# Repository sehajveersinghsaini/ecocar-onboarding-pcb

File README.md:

# EcoCar Onboarding PCB (STM32F103)

My onboarding board for the EcoCar team (Electrical), 2026–27 season. It's an STM32F103C8T6 development board powered and programmed over USB-C/SWD, with 10 LEDs, buttons, a potentiometer and headers for I2C, SPI and UART.

**Status:** design finished and checked (ERC 0, DRC 0, schematic/PCB parity 0). Waiting for the Electrical Lead's review before ordering. Assembly and firmware come next.

## What's on the board

| Block | Parts | Notes |
|---|---|---|
| MCU | U1 STM32F103C8T6 (LQFP-48) | 8 MHz crystal Y1 with 20 pF load caps (C10, C11) |
| Power | J3 USB-C, U2 AMS1117-3.3 | 5 V from USB → 3.3 V. C8 10 µF in, C9 22 µF out |
| Decoupling | C1–C4 100 nF, C5 4.7 µF | One 100 nF right next to each VDD/VBAT pin |
| Analog supply | FB1 ferrite bead, C6 10 nF, C7 1 µF | Filters 3.3 V into VDDA |
| USB | R3, R4 5.1 kΩ on CC1/CC2, R5 1.5 kΩ D+ pull-up | USB full speed on PA11/PA12 |
| Programming | J2 SWD header, SW1 reset, J1 BOOT0 jumper | R1/R2 10 kΩ pull-downs on BOOT0/BOOT1 |
| LEDs | D1–D10 (4 red, 3 yellow, 3 green), 330 Ω each | D6–D10 are on timer channels for PWM |
| Inputs | SW2–SW4 push buttons, RV1 10 kΩ potentiometer | Buttons use internal pull-ups; pot goes to ADC PA0 |
| Headers | J4 OLED (I2C1), J5 SPI2, J6 UART1, J7 I2C2, J8 power | 4.7 kΩ pull-ups on both I2C buses (R16–R19) |

## Pin map

| MCU pin | Function | Connected to |
|---|---|---|
| PA0 | ADC1_IN0 | RV1 wiper |
| PA1–PA5 | GPIO out | LED1–LED5 (D1–D5) |
| PA6, PA7, PB0, PB1, PA8 | TIM PWM | LED_PWM1–5 (D6–D10) |
| PA9 / PA10 | USART1 TX / RX | J6 |
| PA11 / PA12 | USB D− / D+ | J3 |
| PA13 / PA14 | SWDIO / SWCLK | J2 |
| PB5, PB8, PB9 | GPIO in | BTN1–BTN3 (SW2–SW4) |
| PB6 / PB7 | I2C1 SCL / SDA | J4 (OLED) |
| PB10 / PB11 | I2C2 SCL / SDA | J7 |
| PB12–PB15 | SPI2 CS / SCK / MISO / MOSI | J5 |
| PD0 / PD1 | HSE in / out | Y1 8 MHz |

## Header pinouts (pin 1 first)

- **J2 SWD:** 3V3, SWCLK, SWDIO, NRST, GND
- **J4 OLED:** GND, 3V3, SCL, SDA
- **J5 SPI2:** GND, 3V3, SCK, MISO, MOSI, CS
- **J6 UART1:** GND, TX, RX
- **J7 I2C2:** GND, 3V3, SCL, SDA
- **J8 Power:** 5V, 5V, 3V3, 3V3, GND, GND
- **J1 BOOT0:** BOOT0, 3V3 (jumper on = boot from system memory)

## Layout

- 80 × 60 mm, 2 layers, 1.6 mm FR4
- Ground pour on both layers, stitched with vias across the board
- Top layer routes horizontally, bottom layer vertically, with vias to change direction (short fan-outs at the pins)
- Signal traces 0.25 mm, 3.3 V 0.4 mm, 5 V 0.5 mm, 0.2 mm clearance
- 0603 or larger passives, no BGA
- The USB-C connector's mouth sits flush with the right edge. Its silkscreen line was trimmed so it doesn't hang off the board, which is why there's one DRC exclusion (library mismatch on J3).

## Files

- `hardware/ecocar_onboarding/` — KiCad 10 project (schematic, PCB, schematic PDF)
- `firmware/ecocar_onboarding.ioc` — STM32CubeMX pin configuration
- `docs/board_3d.png` — 3D render

## How it was made

Following the Phil's Lab KiCad STM32 tutorial and the EcoCar onboarding requirements.

## Next steps

1. Design review with the Electrical Lead
2. Order the board and solder it by hand
3. Firmware in STM32CubeIDE: LED patterns, potentiometer → PWM brightness, buttons, USB serial messages, OLED

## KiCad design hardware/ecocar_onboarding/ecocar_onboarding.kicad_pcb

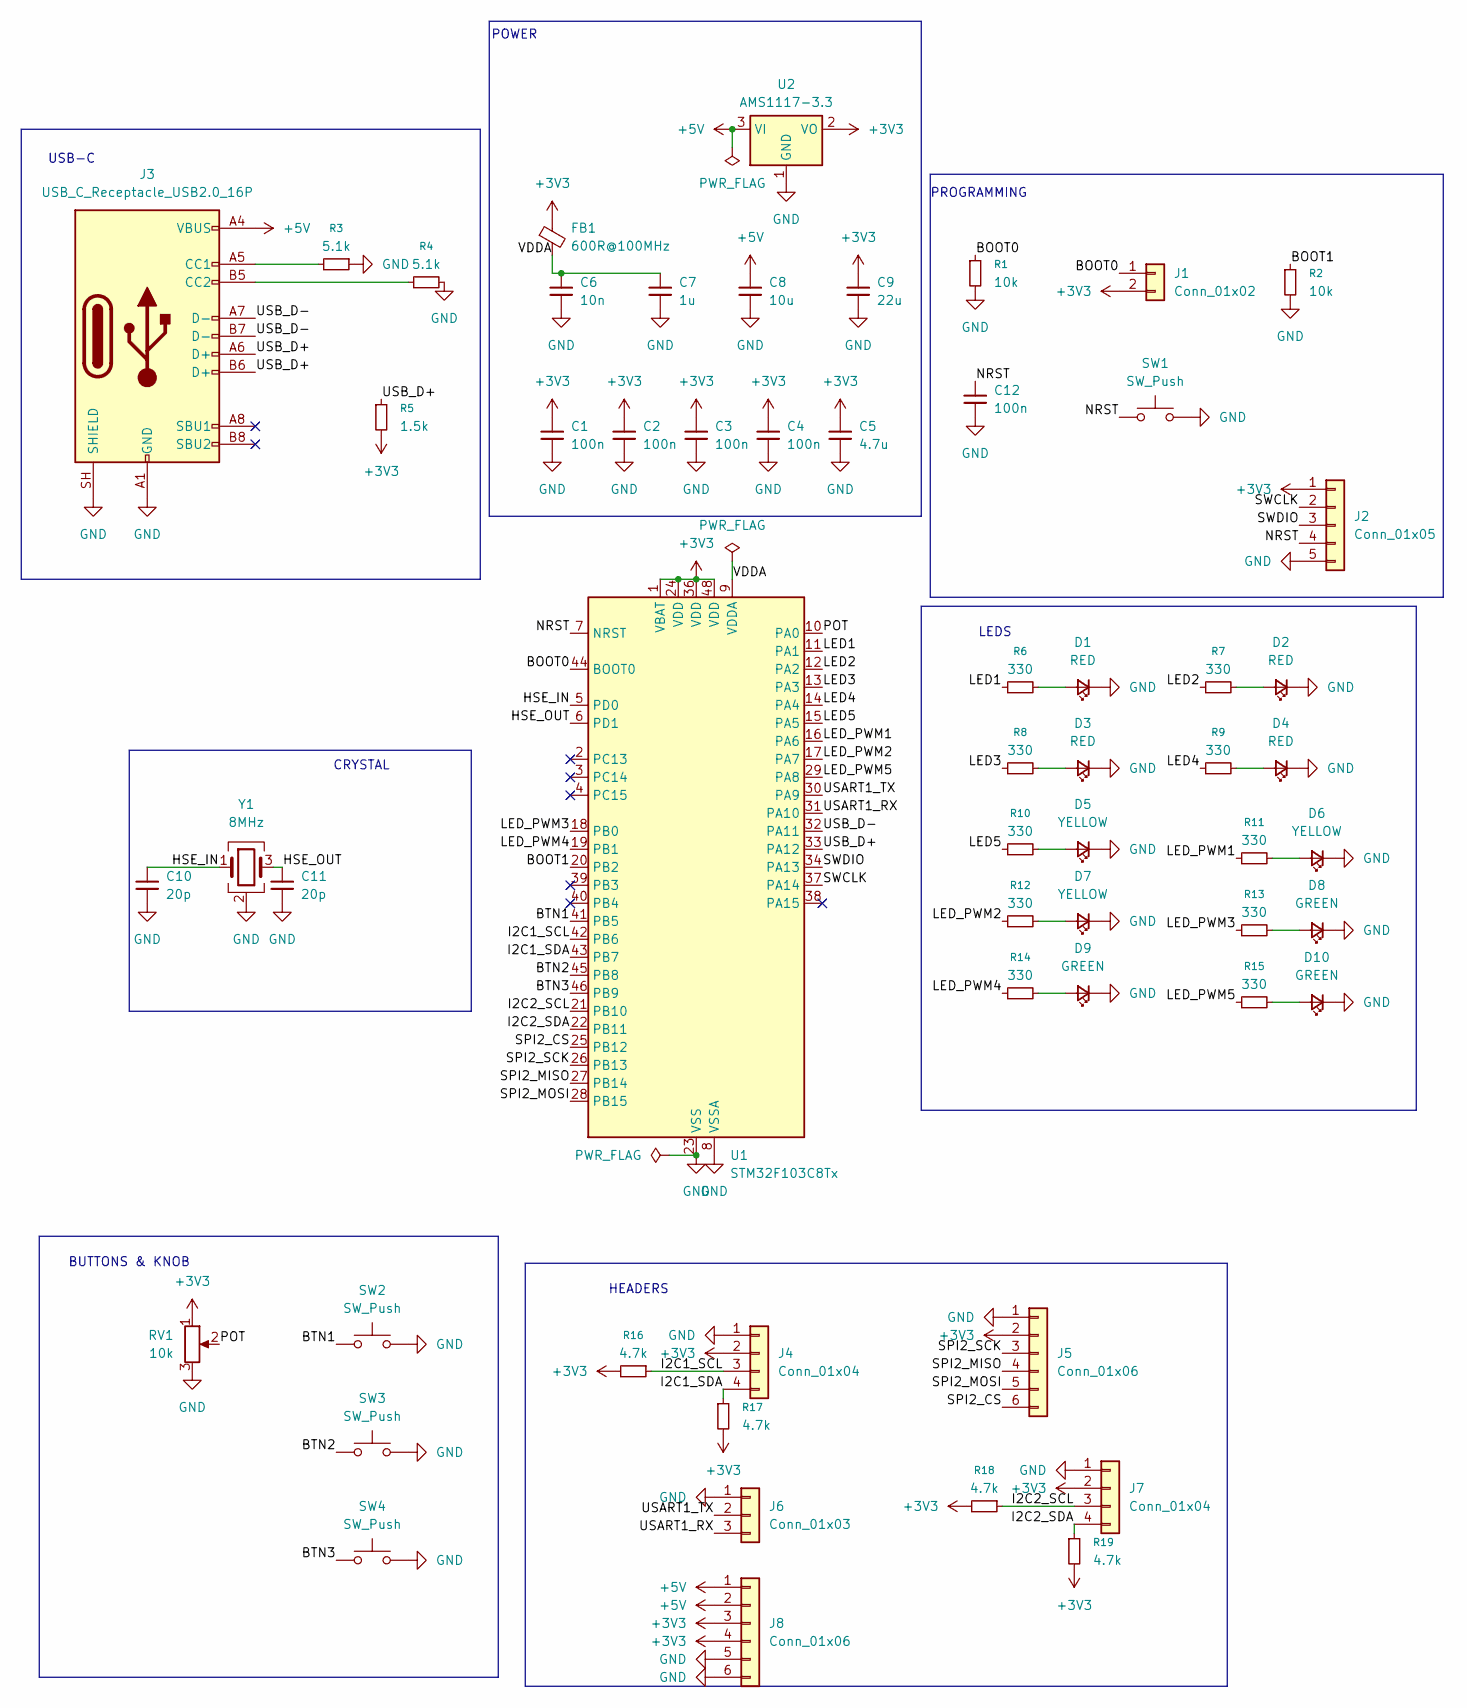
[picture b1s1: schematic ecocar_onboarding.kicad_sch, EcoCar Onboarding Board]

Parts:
C1, C2, C3, C4, C12: 100n; C_0603_1608Metric
C5: 4.7u; C_0805_2012Metric
C6: 10n; C_0603_1608Metric
C7: 1u; C_0603_1608Metric
C8: 10u; C_0805_2012Metric
C9: 22u; C_0805_2012Metric
C10, C11: 20p; C_0603_1608Metric
D1, D2, D3, D4: RED; LED_0603_1608Metric
D5, D6, D7: YELLOW; LED_0603_1608Metric
D8, D9, D10: GREEN; LED_0603_1608Metric
FB1: 600R@100MHz; L_0603_1608Metric
J1: Conn_01x02; PinHeader_1x02_P2.54mm_Vertical
J2: Conn_01x05; PinHeader_1x05_P2.54mm_Vertical
J3: USB_C_Receptacle_USB2.0_16P; USB_C_Receptacle_HRO_TYPE-C-31-M-12
J4, J7: Conn_01x04; PinHeader_1x04_P2.54mm_Vertical
J5, J8: Conn_01x06; PinHeader_1x06_P2.54mm_Vertical
J6: Conn_01x03; PinHeader_1x03_P2.54mm_Vertical
R1, R2: 10k; R_0603_1608Metric
R3, R4: 5.1k; R_0603_1608Metric
R5: 1.5k; R_0603_1608Metric
R6, R7, R8, R9, R10, R11, R12, R13, R14, R15: 330; R_0603_1608Metric
R16, R17, R18, R19: 4.7k; R_0603_1608Metric
RV1: 10k; Potentiometer_Bourns_3386P_Vertical
SW1, SW2, SW3, SW4: SW_Push; SW_PUSH_6mm
U1: STM32F103C8Tx; LQFP-48_7x7mm_P0.5mm
U2: AMS1117-3.3; SOT-223-3_TabPin2
Y1: 8MHz; Crystal_SMD_3225-4Pin_3.2x2.5mm

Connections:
+3V3: C1.1, C2.1, C3.1, C4.1, C5.1, C9.1, FB1.1, J1.2, J2.1, J4.2, J5.2, J7.2, J8.3, J8.4, R5.2, R16.2, R17.2, R18.2, R19.2, RV1.1, U1.1 (VBAT), U1.24 (VDD), U1.36 (VDD), U1.48 (VDD), U2.2 (VO)
+5V: C8.1, J3.A4 (VBUS), J3.A9 (VBUS), J3.B4 (VBUS), J3.B9 (VBUS), J8.1, J8.2, U2.3 (VI)
/BOOT0: J1.1, R1.1, U1.44 (BOOT0)
/BOOT1: R2.1, U1.20 (PB2)
/BTN1: SW2.1, U1.41 (PB5)
/BTN2: SW3.1, U1.45 (PB8)
/BTN3: SW4.1, U1.46 (PB9)
/HSE_IN: C10.1, U1.5 (PD0), Y1.1
/HSE_OUT: C11.1, U1.6 (PD1), Y1.3
/I2C1_SCL: J4.3, R16.1, U1.42 (PB6)
/I2C1_SDA: J4.4, R17.1, U1.43 (PB7)
/I2C2_SCL: J7.3, R18.1, U1.21 (PB10)
/I2C2_SDA: J7.4, R19.1, U1.22 (PB11)
/LED1: R6.1, U1.11 (PA1)
/LED2: R7.1, U1.12 (PA2)
/LED3: R8.1, U1.13 (PA3)
/LED4: R9.1, U1.14 (PA4)
/LED5: R10.1, U1.15 (PA5)
/LED_PWM1: R11.1, U1.16 (PA6)
/LED_PWM2: R12.1, U1.17 (PA7)
/LED_PWM3: R13.1, U1.18 (PB0)
/LED_PWM4: R14.1, U1.19 (PB1)
/LED_PWM5: R15.1, U1.29 (PA8)
/NRST: C12.1, J2.4, SW1.1, U1.7 (NRST)
/POT: RV1.2, U1.10 (PA0)
/SPI2_CS: J5.6, U1.25 (PB12)
/SPI2_MISO: J5.4, U1.27 (PB14)
/SPI2_MOSI: J5.5, U1.28 (PB15)
/SPI2_SCK: J5.3, U1.26 (PB13)
/SWCLK: J2.2, U1.37 (PA14)
/SWDIO: J2.3, U1.34 (PA13)
/USART1_RX: J6.3, U1.31 (PA10)
/USART1_TX: J6.2, U1.30 (PA9)
/USB_D+: J3.A6 (D+), J3.B6 (D+), R5.1, U1.33 (PA12)
/USB_D-: J3.A7 (D-), J3.B7 (D-), U1.32 (PA11)
/VDDA: C6.1, C7.1, FB1.2, U1.9 (VDDA)
GND: C1.2, C2.2, C3.2, C4.2, C5.2, C6.2, C7.2, C8.2, C9.2, C10.2, C11.2, C12.2, D1.1 (K), D2.1 (K), D3.1 (K), D4.1 (K), D5.1 (K), D6.1 (K), D7.1 (K), D8.1 (K), D9.1 (K), D10.1 (K), J2.5, J3.A1 (GND), J3.A12 (GND), J3.B1 (GND), J3.B12 (GND), J3.SH (SHIELD), J4.1, J5.1, J6.1, J7.1, J8.5, J8.6, R1.2, R2.2, R3.1, R4.2, RV1.3, SW1.2, SW2.2, SW3.2, SW4.2, U1.8 (VSSA), U1.23 (VSS), U1.35 (VSS), U1.47 (VSS), U2.1 (GND), Y1.2 (G), Y1.4 (G)
unnamed: D1.2 (A), R6.2
unnamed: D2.2 (A), R7.2
unnamed: D3.2 (A), R8.2
unnamed: D4.2 (A), R9.2
unnamed: D5.2 (A), R10.2
unnamed: D6.2 (A), R11.2
unnamed: D7.2 (A), R12.2
unnamed: D8.2 (A), R13.2
unnamed: D9.2 (A), R14.2
unnamed: D10.2 (A), R15.2
unnamed: J3.A5 (CC1), R3.2
unnamed: J3.B5 (CC2), R4.1

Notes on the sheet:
PROGRAMMING
POWER
CRYSTAL
USB-C
HEADERS
BUTTONS & KNOB
LEDS

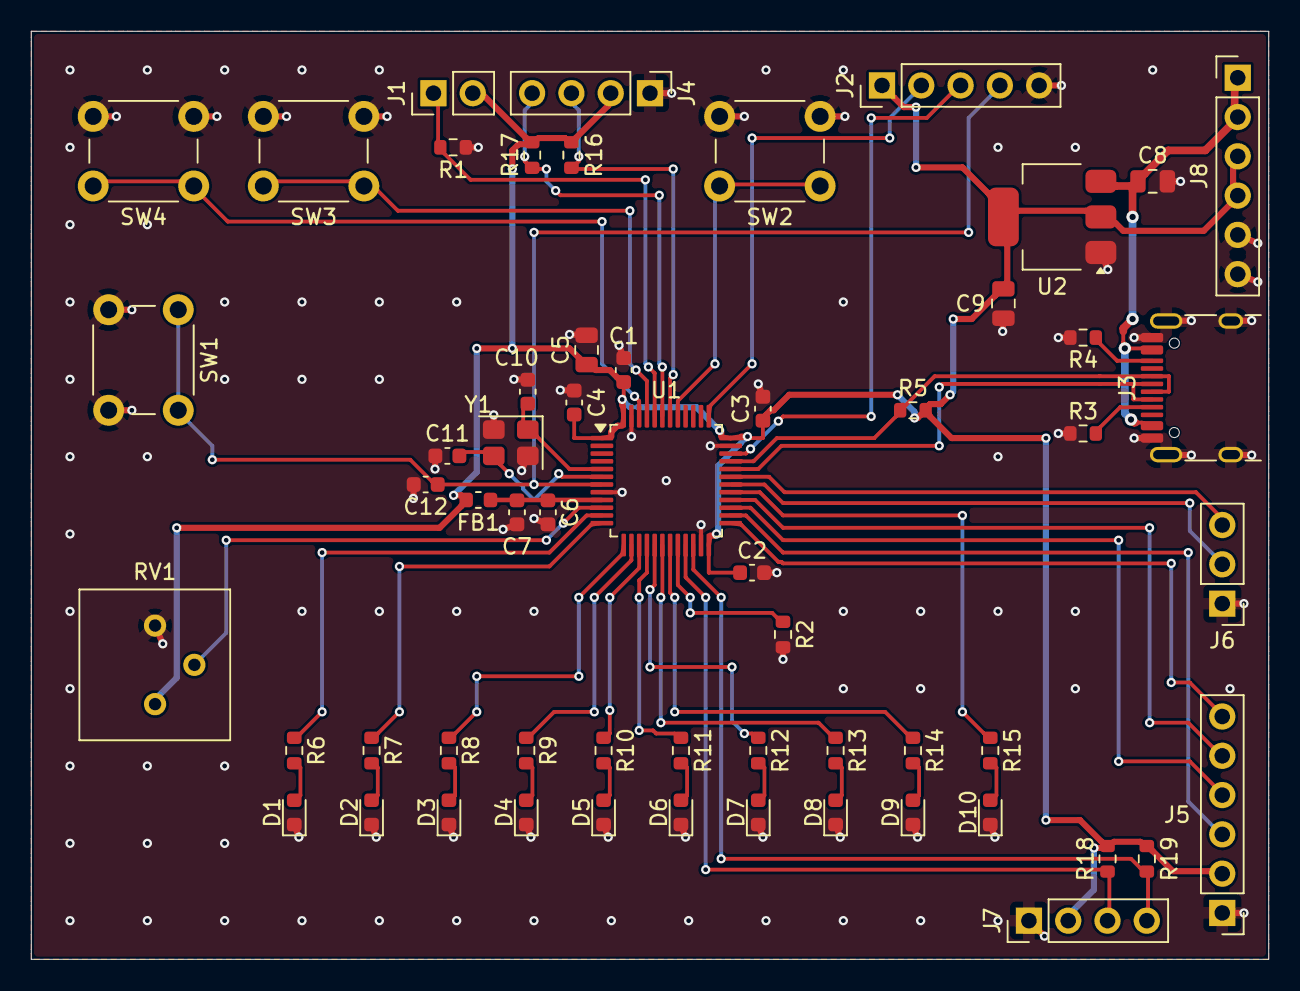
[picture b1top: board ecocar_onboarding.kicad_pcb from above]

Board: 2 copper layers, 80.0 x 60.0 mm, 58 parts (0 on the bottom side), 49 nets.

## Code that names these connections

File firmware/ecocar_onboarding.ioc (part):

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Mcu.Name=STM32F103C(8-B)Tx
Mcu.Package=LQFP48
Mcu.UserName=STM32F103C8Tx
PA0-WKUP.GPIOParameters=GPIO_Label
PA0-WKUP.GPIO_Label=POT
PA0-WKUP.Signal=ADCx_IN0
PA1.GPIOParameters=GPIO_Label
PA1.GPIO_Label=LED1
PA1.Signal=GPIO_Output
PA10.Mode=Asynchronous
PA10.Signal=USART1_RX
PA11.Mode=Device
PA11.Signal=USB_DM
PA12.Mode=Device
PA12.Signal=USB_DP
PA13.Mode=Serial_Wire
PA13.Signal=SYS_JTMS-SWDIO
PA14.Mode=Serial_Wire
PA14.Signal=SYS_JTCK-SWCLK
PA2.GPIOParameters=GPIO_Label
PA2.GPIO_Label=LED2
PA2.Signal=GPIO_Output
PA3.GPIOParameters=GPIO_Label
PA3.GPIO_Label=LED3
PA3.Signal=GPIO_Output
PA4.GPIOParameters=GPIO_Label
PA4.GPIO_Label=LED4
PA4.Signal=GPIO_Output
PA5.GPIOParameters=GPIO_Label
PA5.GPIO_Label=LED5
PA5.Signal=GPIO_Output
PA6.GPIOParameters=GPIO_Label
PA6.GPIO_Label=LED_PWM1
PA6.Signal=S_TIM3_CH1
PA7.GPIOParameters=GPIO_Label
PA7.GPIO_Label=LED_PWM2
PA7.Signal=S_TIM3_CH2
PA8.GPIOParameters=GPIO_Label
PA8.GPIO_Label=LED_PWM5
PA8.Signal=S_TIM1_CH1
PA9.Mode=Asynchronous
PA9.Signal=USART1_TX
PB0.GPIOParameters=GPIO_Label
PB0.GPIO_Label=LED_PWM3
PB0.Signal=S_TIM3_CH3
PB1.GPIOParameters=GPIO_Label
PB1.GPIO_Label=LED_PWM4
PB1.Signal=S_TIM3_CH4
PB10.Mode=I2C
PB10.Signal=I2C2_SCL
PB11.Mode=I2C
PB11.Signal=I2C2_SDA
PB12.GPIOParameters=GPIO_Label
PB12.GPIO_Label=SPI2_CS
PB12.Signal=GPIO_Output
PB13.Mode=Full_Duplex_Master
PB13.Signal=SPI2_SCK
PB14.Mode=Full_Duplex_Master
PB14.Signal=SPI2_MISO
PB15.Mode=Full_Duplex_Master
PB15.Signal=SPI2_MOSI
PB5.GPIOParameters=GPIO_PuPd,GPIO_Label
PB5.GPIO_Label=BTN1
PB5.GPIO_PuPd=GPIO_PULLUP
PB5.Signal=GPIO_Input
PB6.Mode=I2C
PB6.Signal=I2C1_SCL
PB7.Mode=I2C
PB7.Signal=I2C1_SDA
PB8.GPIOParameters=GPIO_PuPd,GPIO_Label
PB8.GPIO_Label=BTN2
PB8.GPIO_PuPd=GPIO_PULLUP
PB8.Signal=GPIO_Input
PB9.GPIOParameters=GPIO_PuPd,GPIO_Label
PB9.GPIO_Label=BTN3
PB9.GPIO_PuPd=GPIO_PULLUP
PB9.Signal=GPIO_Input
PD0-OSC_IN.Mode=HSE-External-Oscillator
PD0-OSC_IN.Signal=RCC_OSC_IN
PD1-OSC_OUT.Mode=HSE-External-Oscillator
PD1-OSC_OUT.Signal=RCC_OSC_OUT
RCC.SYSCLKFreq_VALUE=72000000
RCC.SYSCLKSource=RCC_SYSCLKSOURCE_PLLCLK
board=custom
